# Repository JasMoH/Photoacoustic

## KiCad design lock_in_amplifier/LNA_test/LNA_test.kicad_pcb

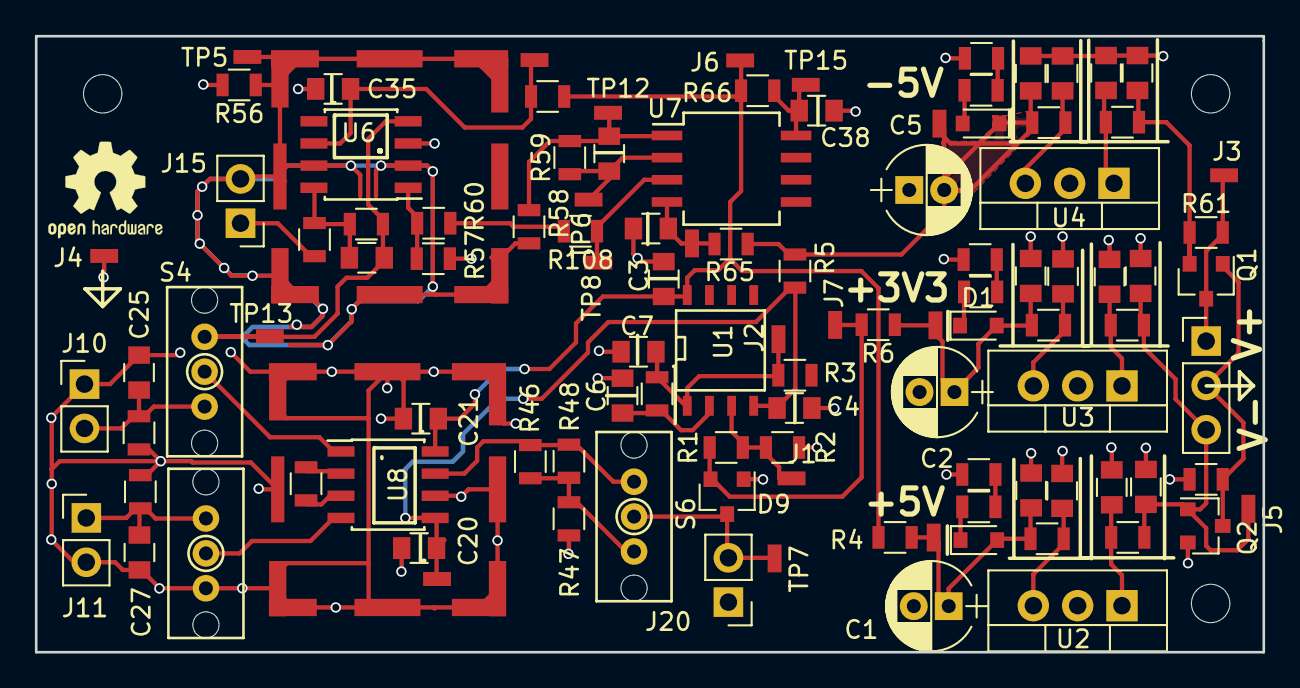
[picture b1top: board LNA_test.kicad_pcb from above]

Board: 2 copper layers, 70.4 x 35.3 mm, 109 parts (0 on the bottom side), 44 nets.

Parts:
C1, C2, C5: 10u; CP_Radial_D5.0mm_P2.00mm
C3, C4, C20, C21, C35, C37, C38: 0.1u; C_0805
C6, C7, C8, C9, C10, C11, C12, C13, C14, C15, C16, C17, C18, C19: 0.1uF; C_0805
C25, C27, C36: 10pF; C_0805
C39: C; C_0805
D1, D2, D3: LED; D_0805
D9: BAT54S; SOT-23
J1: vref-in; tyco_RCU_0603_Probe_Pad
J2: vref; tyco_RCU_0603_Probe_Pad
J3: V-IN; tyco_RCU_0603_Probe_Pad
J4: GND; tyco_RCU_0603_Probe_Pad
J5: V+IN; tyco_RCU_0603_Probe_Pad
J6: +5V; tyco_RCU_0603_Probe_Pad
J7: +3V3; tyco_RCU_0603_Probe_Pad
J8: -5V; tyco_RCU_0603_Probe_Pad
J10: A IN; Pin_Header_Straight_1x02_Pitch2.54mm
J11: B IN; Pin_Header_Straight_1x02_Pitch2.54mm
J12: POWER_IN; Pin_Header_Straight_1x03_Pitch2.54mm
J15: I IN; Pin_Header_Straight_1x02_Pitch2.54mm
J17, J38: RF_Shield_One_Piece; SMS-201
J19: +3V3 OUT; tyco_RCU_0603_Probe_Pad
J20: AMP OUT; Pin_Header_Straight_1x02_Pitch2.54mm
J46: -5V OUT; tyco_RCU_0603_Probe_Pad
J47: +5V OUT; tyco_RCU_0603_Probe_Pad
L1, L2, L3, L4, L5, L6, L7: 10uH; L_0805
Q1, Q2: DMN640L; SOT-23
R1, R2, R60: 10K; R_0805
R3, R4, R5, R6, R56, R57, R61, R62, R63, R65, R108: 0; R_0805
R7, R8, R9, R43, R44, R45, R47, R58, R64: 100; R_0805
R21: 6.04; R_0805
R46: 10k; R_0805
R48: 1M; R_0805
R49, R50: 10M; R_0805
R55: 100M; R_0805
R59, R66: R; R_0805
S4: A / I SEL; SPDT_OS102011MS2QN1
S5: B SEL; SPDT_OS102011MS2QN1
S6: LNA GAIN SEL; SPDT_OS102011MS2QN1
TP5: CURRENT GUARD; tyco_RCU_0603_Probe_Pad
TP6: CURRENT GUARD FB; tyco_RCU_0603_Probe_Pad
TP7: LNA OUT; tyco_RCU_0603_Probe_Pad
TP8: TIA GUARD BUFF IN; tyco_RCU_0603_Probe_Pad
TP11: TIAV+; tyco_RCU_0603_Probe_Pad
TP12: GBUFFOUT; tyco_RCU_0603_Probe_Pad
TP13: TIA_OUT; tyco_RCU_0603_Probe_Pad
TP14: GBUFV-; tyco_RCU_0603_Probe_Pad
TP15: GBUFFV+; tyco_RCU_0603_Probe_Pad
U1: LM833; SOIC-8-N
U2: lm7805; TO-220-3_Vertical
U3: LM7833; TO-220-3_Vertical
U4: lm7905; TO-220-3_Vertical
U6: lmp7721; SOIC-8_3.9x4.9mm_Pitch1.27mm
U7: LM833; SO-8_5.3x6.2mm_Pitch1.27mm
U8: AD8429; SOIC-8_3.9x4.9mm_Pitch1.27mm

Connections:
+3V3: C2.1, C18.1, D1.2, D9.2, J7.1, J19.1, L6.2, R1.1, R6.1, R6.2
+5V: C1.1, C3.2, C19.1, C21.2, D3.2, J6.1, J47.1, L7.2, R4.1, R4.2, R63.2, R66.1, U1.8, U8.8
-5V: C4.2, C5.2, C17.1, C20.1, D2.1, J8.1, J46.1, L5.2, R5.1, R5.2, R65.2, U1.4, U8.5
/sheet5A330121/GND_IN: J12.2, Q1.1, Q2.3, R62.2
/sheet5A330121/V+_IN: C8.1, C9.1, J5.1, J12.3, L2.1, L3.2, Q2.1
/sheet5A330121/V-_IN: J3.1, J12.1, Q1.3, R61.2
/sheet5A330123/GUARD: J15.2, J17.1, R56.1, R58.2, TP5.1, U6.2, U6.7
/sheet5A330123/I_IN: J15.1, R64.2
/sheet5A330123/amplifie_signal: D9.3, J20.2, S6.2, TP7.1
/sheet5A330123/in+: C27.2, J11.1, R50.1, S5.1
/sheet5A330123/in-: C25.2, J10.2, R49.1, S4.3
GND: C1.2, C2.2, C3.1, C4.1, C5.1, C6.2, C7.2, C8.2, C9.2, C10.2, C11.2, C12.2, C13.2, C14.2, C15.2, C16.2, C17.2, C18.2, C19.2, C20.2, C21.1, C25.1, C27.1, C35.1, C37.2, C38.1, D9.1, J4.1, J10.1, J11.2, J20.1, J38.1, Q2.2, R2.2, R8.2, R43.2, R45.2, R47.2, R49.2, R50.2, R56.2, R57.1, R62.1, S5.3, U2.2, U3.2, U4.2, U6.3, U8.6
unnamed: C6.1, L1.2, U1.2
unnamed: C7.1, J2.1, L1.1, R3.2, U1.1
unnamed: C10.1, L4.2, Q1.2, R61.1
unnamed: C11.1, L2.2, U2.1
unnamed: C12.1, L3.1, U3.1
unnamed: C13.1, L4.1, U4.1
unnamed: C14.1, L5.1, U4.3
unnamed: C15.1, L6.1, U3.3
unnamed: C16.1, L7.1, U2.3
unnamed: C35.2, R63.1, TP11.1, U6.6
unnamed: C36.1, R55.1, S4.1, TP13.1, U6.4
unnamed: C36.2, R55.2, R64.1, U6.8
unnamed: C37.1, R65.1, TP14.1, U7.4
unnamed: C38.2, R66.2, TP15.1, U7.8
unnamed: C39.1, R59.1, TP6.1, U7.2
unnamed: C39.2, R58.1, R59.2, TP12.1, U7.1
unnamed: D1.1, R44.1
unnamed: D2.2, R7.1
unnamed: D3.1, R9.1
unnamed: J1.1, R1.2, R2.1, U1.3
unnamed: R7.2, R8.1
unnamed: R21.1, U8.3
unnamed: R21.2, U8.2
unnamed: R9.2, R43.1
unnamed: R44.2, R45.1
unnamed: R46.1, R48.1, S6.1, U8.7
unnamed: R46.2, R47.1, R48.2, S6.3
unnamed: R57.2, R60.2, U6.1
unnamed: R108.1, TP8.1, U7.3
unnamed: R60.1, R108.2
unnamed: S4.2, U8.1
unnamed: S5.2, U8.4

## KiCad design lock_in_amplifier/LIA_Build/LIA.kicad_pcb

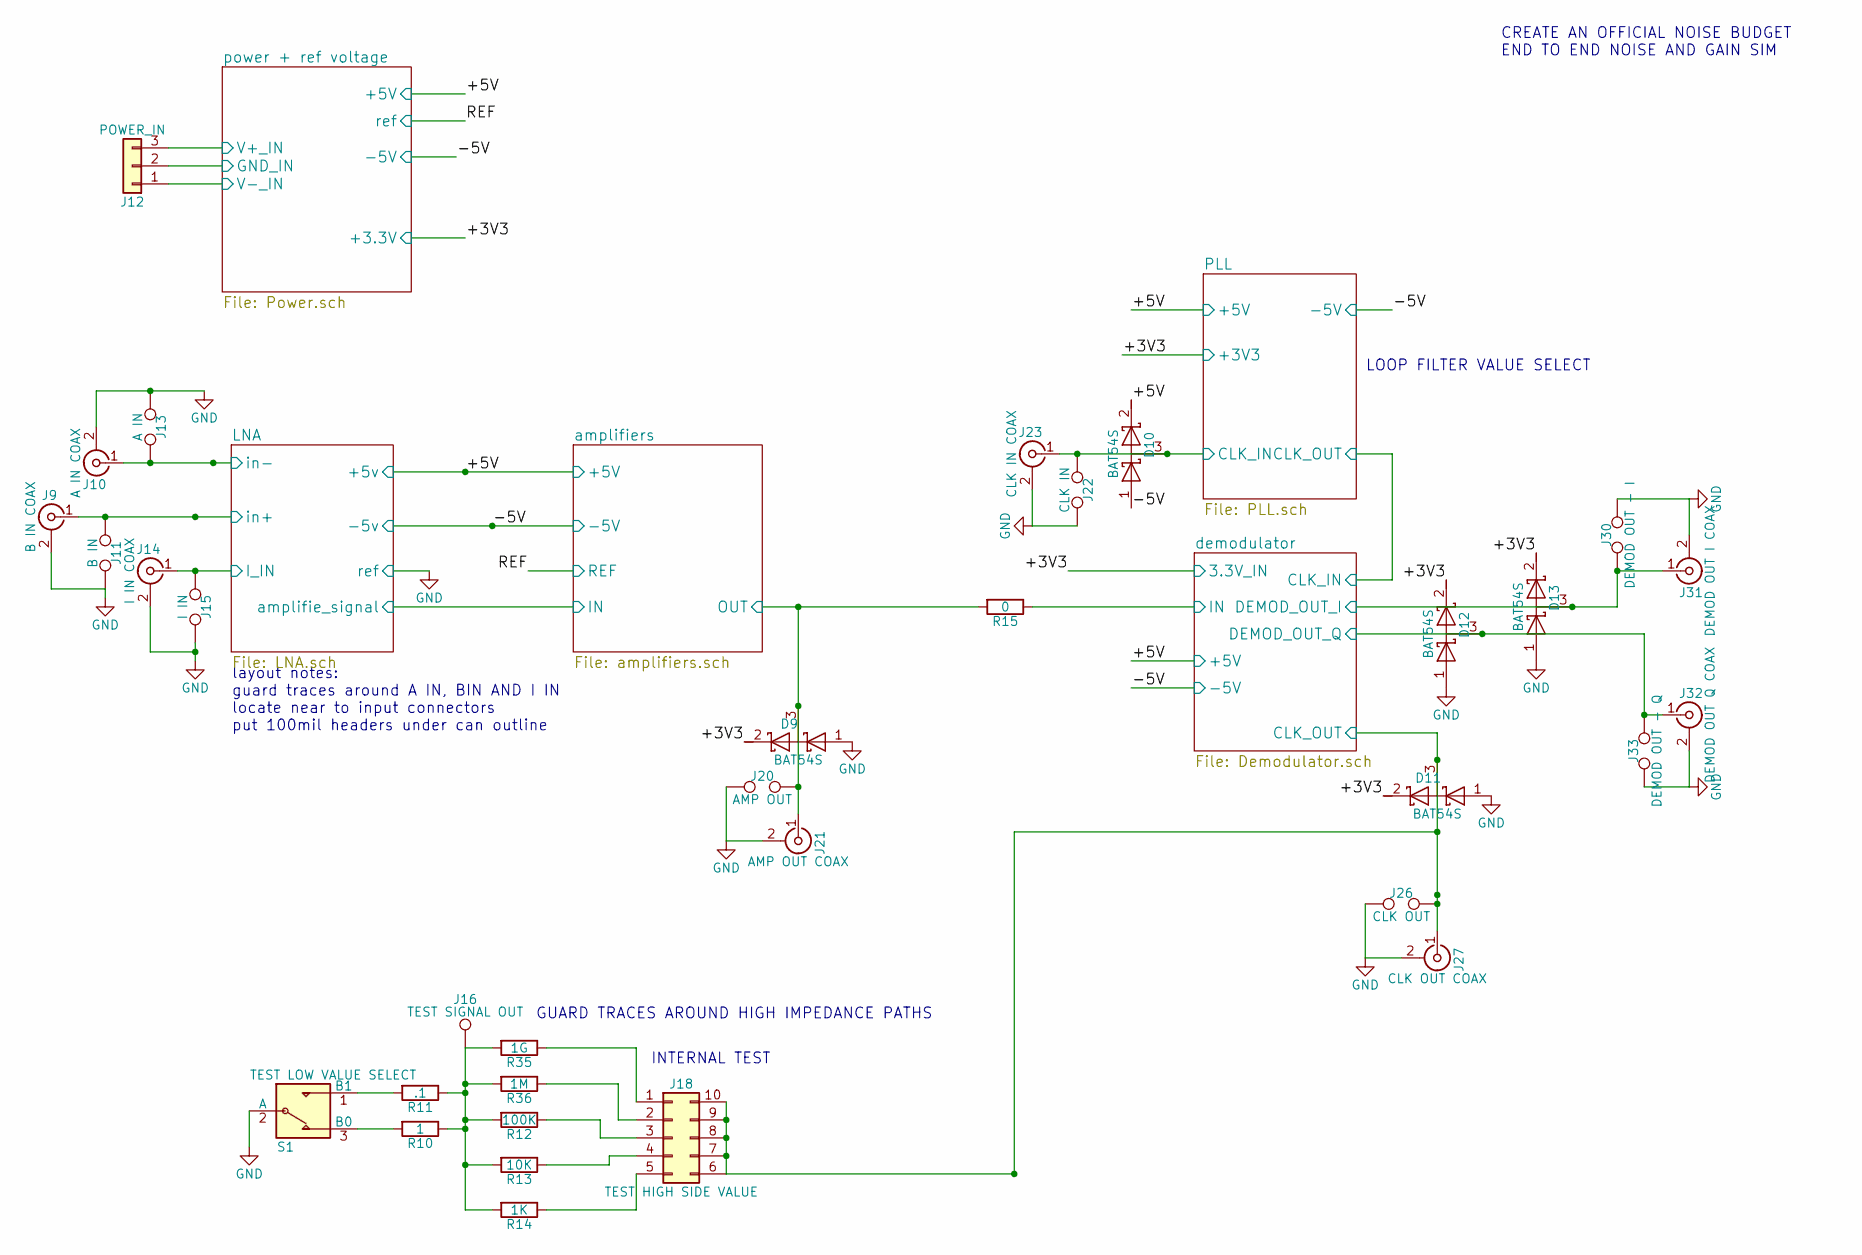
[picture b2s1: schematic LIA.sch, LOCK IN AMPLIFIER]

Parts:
D9, D10, D11, D12, D13: BAT54S; SOT-23
J9: B IN COAX; SMA_THT_Jack_Straight
J10: A IN COAX; SMA_THT_Jack_Straight
J11: B IN; Pin_Header_Straight_1x02_Pitch2.54mm
J12: POWER_IN; Pin_Header_Straight_1x03_Pitch2.54mm
J13: A IN; Pin_Header_Straight_1x02_Pitch2.54mm
J14: I IN COAX; SMA_THT_Jack_Straight
J15: I IN; Pin_Header_Straight_1x02_Pitch2.54mm
J16: TEST SIGNAL OUT; Pin_Header_Straight_1x01_Pitch1.00mm
J18: TEST HIGH SIDE VALUE; Pin_Header_Straight_2x05_Pitch2.54mm
J20: AMP OUT; Pin_Header_Straight_1x02_Pitch2.54mm
J21: AMP OUT COAX; SMA_THT_Jack_Straight
J22: CLK IN; Pin_Header_Straight_1x02_Pitch2.54mm
J23: CLK IN COAX; SMA_THT_Jack_Straight
J26: CLK OUT; Pin_Header_Straight_1x02_Pitch2.54mm
J27: CLK OUT COAX; SMA_THT_Jack_Straight
J30: DEMOD OUT - I; Pin_Header_Straight_1x02_Pitch2.54mm
J31: DEMOD OUT I COAX; SMA_THT_Jack_Straight
J32: DEMOD OUT Q COAX; SMA_THT_Jack_Straight
J33: DEMOD OUT - Q; Pin_Header_Straight_1x02_Pitch2.54mm
R10: 1; R_0805
R11: .1; R_0805
R12: 100K; R_0805
R13: 10K; R_0805
R14: 1K; R_0805
R15: 0; R_0805
R35: 1G; R_Axial_DIN0414_L11.9mm_D4.5mm_P15.24mm_Horizontal
R36: 1M; R_0805
S1: TEST LOW VALUE SELECT; Pin_Header_Straight_1x03_Pitch2.54mm

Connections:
+3V3: D9.2 (K), D11.2 (K), D12.2 (K), D13.2 (K); also elsewhere on the board
/LNA/I_IN: J14.1 (In), J15.1; also elsewhere on the board
/LNA/in+: J9.1 (In), J11.1; also elsewhere on the board
/LNA/in-: J10.1 (In), J13.2; also elsewhere on the board
/PLL/CLK_IN: D10.3 (common), J22.2, J23.1 (In); also elsewhere on the board
/amplifiers/OUT: D9.3 (common), J20.2, J21.1 (In), R15.2; also elsewhere on the board
/demodulator/CLK_OUT: D11.3 (common), J18.6, J18.7, J18.8, J18.9, J18.10, J26.2, J27.1 (In); also elsewhere on the board
/demodulator/DEMOD_OUT_I: D13.3 (common), J30.2, J31.1 (In); also elsewhere on the board
/demodulator/DEMOD_OUT_Q: D12.3 (common), J32.1 (In), J33.1; also elsewhere on the board
/demodulator/IN: R15.1; also elsewhere on the board
/power + ref voltage/GND_IN: J12.2; also elsewhere on the board
/power + ref voltage/V+_IN: J12.3; also elsewhere on the board
/power + ref voltage/V-_IN: J12.1; also elsewhere on the board
unnamed: J16.1, R10.1, R11.1, R12.2, R13.2, R14.2, R35.2, R36.2
unnamed: J18.1, R35.1
unnamed: J18.2, R36.1
unnamed: J18.3, R12.1
unnamed: J18.4, R13.1
unnamed: J18.5, R14.1
unnamed: R10.2, S1.3 (B0)
unnamed: R11.2, S1.1 (B1)

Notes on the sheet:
CREATE AN OFFICIAL NOISE BUDGET END TO END NOISE AND GAIN SIM
layout notes: guard traces around A IN, BIN AND I IN locate near to input connectors put 100mil headers under can outline
INTERNAL TEST
GUARD TRACES AROUND HIGH IMPEDANCE PATHS
LOOP FILTER VALUE SELECT

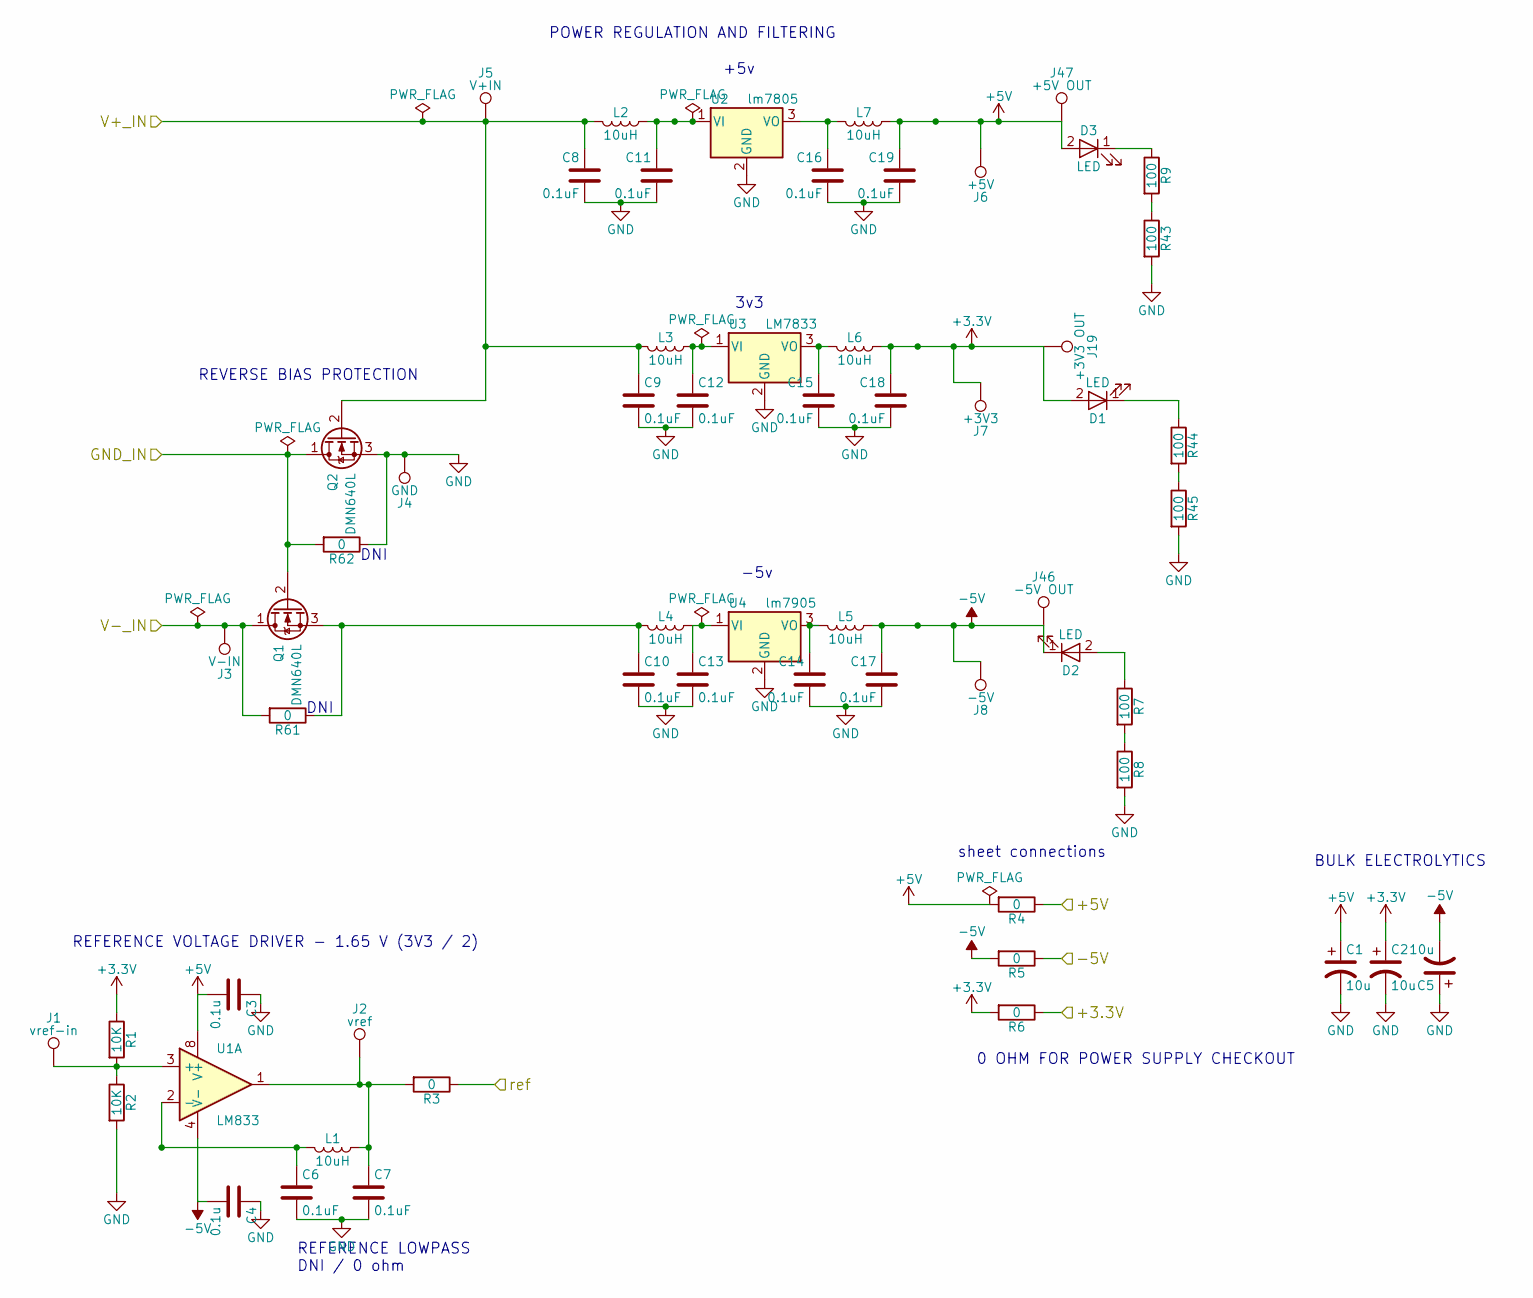
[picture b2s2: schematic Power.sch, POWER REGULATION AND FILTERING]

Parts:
C1, C2, C5: 10u; CP_Radial_D5.0mm_P2.00mm
C3, C4: 0.1u; C_0805
C6, C7, C8, C9, C10, C11, C12, C13, C14, C15, C16, C17, C18, C19: 0.1uF; C_0805
D1, D2, D3: LED; D_0805
J1: vref-in; tyco_RCU_0603_Probe_Pad
J2: vref; tyco_RCU_0603_Probe_Pad
J3: V-IN; tyco_RCU_0603_Probe_Pad
J4: GND; tyco_RCU_0603_Probe_Pad
J5: V+IN; tyco_RCU_0603_Probe_Pad
J6: +5V; tyco_RCU_0603_Probe_Pad
J7: +3V3; tyco_RCU_0603_Probe_Pad
J8: -5V; tyco_RCU_0603_Probe_Pad
J19: +3V3 OUT; tyco_RCU_0603_Probe_Pad
J46: -5V OUT; tyco_RCU_0603_Probe_Pad
J47: +5V OUT; tyco_RCU_0603_Probe_Pad
L1, L2, L3, L4, L5, L6, L7: 10uH; L_0805_HandSoldering
Q1, Q2: DMN640L; SOT-23
R1, R2: 10K; R_0805
R3, R4, R5, R6: 0; R_0805
R7, R8, R9, R43, R44, R45: 100; R_0805
R61, R62: 0
U1: LM833; SOIC-8-N
U2: lm7805; TO-220_Vertical
U3: LM7833; TO-220_Vertical
U4: lm7905; TO-220_Vertical

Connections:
+3V3: C2.1, C18.1, D1.2 (A), J7.1, J19.1, L6.2, R1.1, R6.1, R6.2; also elsewhere on the board
/REF: R3.1; also elsewhere on the board
/power + ref voltage/GND_IN: Q1.2 (G), Q2.1 (D), R62.2; also elsewhere on the board
/power + ref voltage/V+_IN: C8.1, C9.1, J5.1, L2.1, L3.2, Q2.2 (G); also elsewhere on the board
/power + ref voltage/V-_IN: J3.1, Q1.1 (D), R61.2; also elsewhere on the board
unnamed: C6.1, L1.2, U1.2 (-)
unnamed: C7.1, J2.1, L1.1, R3.2, U1.1
unnamed: C10.1, L4.2, Q1.3 (S), R61.1
unnamed: C11.1, L2.2, U2.1 (VI)
unnamed: C12.1, L3.1, U3.1 (VI)
unnamed: C13.1, L4.1, U4.1 (VI)
unnamed: C14.1, L5.1, U4.3 (VO)
unnamed: C15.1, L6.1, U3.3 (VO)
unnamed: C16.1, L7.1, U2.3 (VO)
unnamed: D1.1 (K), R44.1
unnamed: D2.2 (A), R7.1
unnamed: D3.1 (K), R9.1
unnamed: J1.1, R1.2, R2.1, U1.3 (+)
unnamed: R7.2, R8.1
unnamed: R9.2, R43.1
unnamed: R44.2, R45.1

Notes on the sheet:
REFERENCE VOLTAGE DRIVER - 1.65 V (3V3 / 2)
REFERENCE LOWPASS DNI / 0 ohm
BULK ELECTROLYTICS
3v3
+5v
-5v
sheet connections
0 OHM FOR POWER SUPPLY CHECKOUT
POWER REGULATION AND FILTERING
DNI
REVERSE BIAS PROTECTION

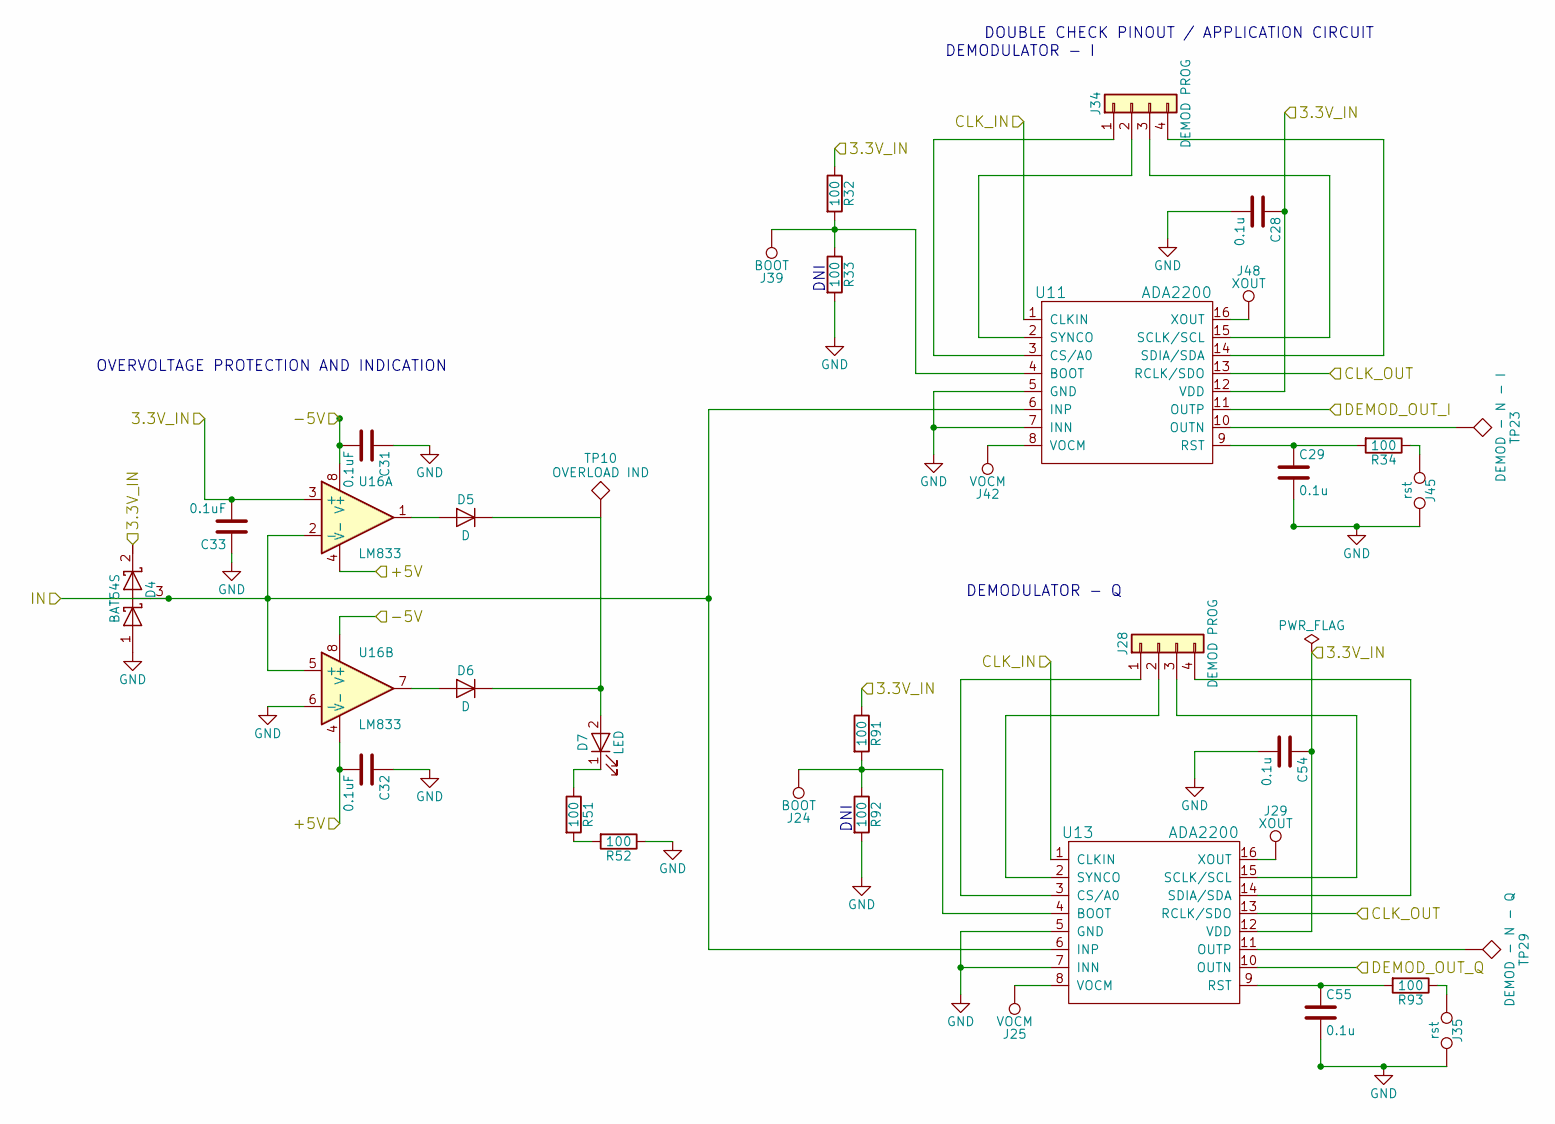
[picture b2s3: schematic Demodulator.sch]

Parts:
C28, C29, C54, C55: 0.1u; C_0805
C31, C32, C33: 0.1uF; C_0805
D4: BAT54S; SOT-23
D5, D6: D; D_0805
D7: LED; LED_0805
J24, J39: BOOT; tyco_RCU_0603_Probe_Pad
J25, J42: VOCM; tyco_RCU_0603_Probe_Pad
J28, J34: DEMOD PROG; Pin_Header_Straight_1x04_Pitch2.54mm
J29, J48: XOUT; tyco_RCU_0603_Probe_Pad
J35, J45: rst; Pin_Header_Straight_1x02_Pitch2.54mm
R32, R33, R34, R51, R52, R91, R92, R93: 100; R_0805
TP10: OVERLOAD IND; tyco_RCU_0603_Probe_Pad
TP23: DEMOD - N - I; tyco_RCU_0603_Probe_Pad
TP29: DEMOD - N - Q; tyco_RCU_0603_Probe_Pad
U11, U13: ADA2200; TSSOP-20_4.4x6.5mm_Pitch0.65mm
U16: LM833; SO-8_5.3x6.2mm_Pitch1.27mm

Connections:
+3V3: C28.1, C33.2, C54.1, D4.2 (K), R32.1, R91.1, U11.12 (VDD), U13.12 (VDD), U16.3 (+); also elsewhere on the board
/demodulator/CLK_IN: U11.1 (CLKIN), U13.1 (CLKIN); also elsewhere on the board
/demodulator/CLK_OUT: U11.13 (RCLK/SDO), U13.13 (RCLK/SDO); also elsewhere on the board
/demodulator/DEMOD_OUT_I: U11.11 (OUTP); also elsewhere on the board
/demodulator/DEMOD_OUT_Q: U13.10 (OUTN); also elsewhere on the board
/demodulator/IN: D4.3 (common), U11.6 (INP), U13.6 (INP), U16.2 (-), U16.5 (+); also elsewhere on the board
unnamed: C29.1, R34.2, U11.9 (RST)
unnamed: C55.1, R93.2, U13.9 (RST)
unnamed: D5.1 (K), D6.1 (K), D7.2 (A), TP10.1
unnamed: D5.2 (A), U16.1
unnamed: D6.2 (A), U16.7
unnamed: D7.1 (K), R51.1
unnamed: J24.1, R91.2, R92.1, U13.4 (BOOT)
unnamed: J25.1, U13.8 (VOCM)
unnamed: J28.1, U13.3 (CS/A0)
unnamed: J28.2, U13.2 (SYNCO)
unnamed: J28.3, U13.15 (SCLK/SCL)
unnamed: J28.4, U13.14 (SDIA/SDA)
unnamed: J29.1, U13.16 (XOUT)
unnamed: J34.1, U11.3 (CS/A0)
unnamed: J34.2, U11.2 (SYNCO)
unnamed: J34.3, U11.15 (SCLK/SCL)
unnamed: J34.4, U11.14 (SDIA/SDA)
unnamed: J35.1, R93.1
unnamed: J39.1, R32.2, R33.1, U11.4 (BOOT)
unnamed: J42.1, U11.8 (VOCM)
unnamed: J45.1, R34.1
unnamed: J48.1, U11.16 (XOUT)
unnamed: R51.2, R52.2
unnamed: TP23.1, U11.10 (OUTN)
unnamed: TP29.1, U13.11 (OUTP)

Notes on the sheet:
DNI
DOUBLE CHECK PINOUT / APPLICATION CIRCUIT
DEMODULATOR - I
OVERVOLTAGE PROTECTION AND INDICATION
DEMODULATOR - Q

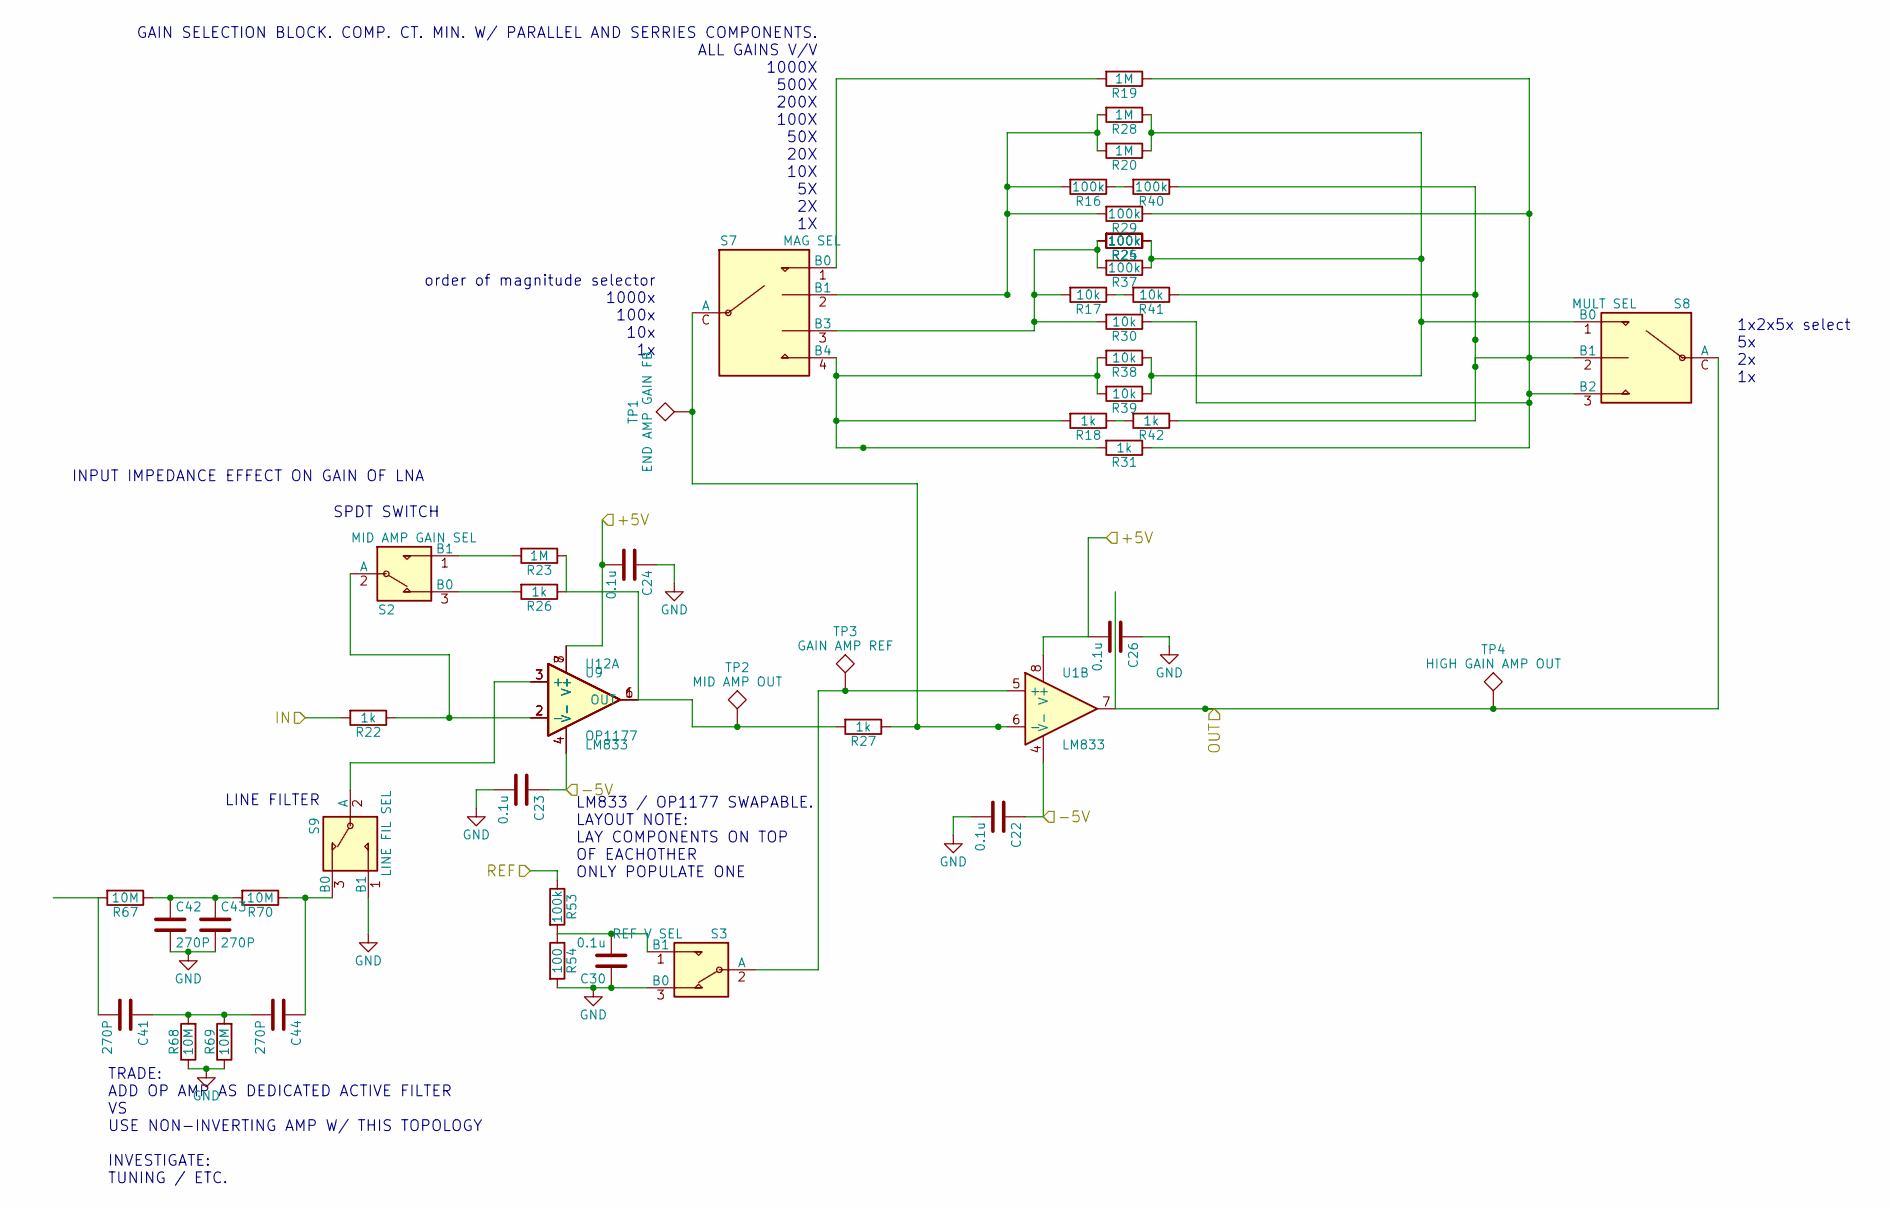
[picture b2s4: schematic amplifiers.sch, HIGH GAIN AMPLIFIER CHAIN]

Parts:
C22, C23, C24, C26, C30: 0.1u; C_0805
C41, C42, C43, C44: 270P
R16, R24, R25, R29, R37, R40: 100k; R_0805
R17, R30, R38, R39, R41: 10k; R_0805
R18, R22, R26, R27, R31, R42: 1k; R_0805
R19, R20, R23, R28: 1M; R_0805
R53: 100k
R54: 100
R67, R68, R69, R70: 10M
S2: MID AMP GAIN SEL; SPDT_OS102011MS2QN1
S3: REF V SEL; SPDT_OS102011MS2QN1
S7: MAG SEL; SP4T_C&K_SS-14D0839-VG
S8: MULT SEL; SP3T_CK_SS-14D0839-VG
S9: LINE FIL SEL; SPDT_OS102011MS2QN1
TP1: END AMP GAIN FB
TP2: MID AMP OUT
TP3: GAIN AMP REF
TP4: HIGH GAIN AMP OUT
U1: LM833; SOIC-8-N
U9: OP1177; MSOP-8-1EP_3x3mm_Pitch0.65mm
U12: LM833

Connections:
/REF: R53.1; also elsewhere on the board
/amplifiers/IN: R22.2; also elsewhere on the board
/amplifiers/OUT: S8.C (A), TP4.1, U1.7; also elsewhere on the board
unnamed: C30.2, R53.2, R54.1, S3.1 (B1)
unnamed: C41.1, C44.2, R68.2, R69.2
unnamed: C42.1, C43.1, R67.1, R70.2
unnamed: R16.1, R40.2
unnamed: R16.2, R20.2, R28.2, R29.2, S7.2 (B1)
unnamed: R17.1, R41.2
unnamed: R17.2, R24.2, R25.2, R30.2, R37.2, S7.3 (B3)
unnamed: R18.1, R42.2
unnamed: R18.2, R31.2, R38.2, R39.2, S7.4 (B4)
unnamed: R19.1, R29.1, R30.1, R31.1, R40.1, R41.1, R42.1, S8.2 (B1), S8.3 (B2)
unnamed: R19.2, S7.1 (B0)
unnamed: R20.1, R24.1, R25.1, R28.1, R37.1, R38.1, R39.1, S8.1 (B0)
unnamed: R23.1, R26.1, R27.2, TP2.1, U9.6 (OUT), U12.1
unnamed: R23.2, S2.1 (B1)
unnamed: R26.2, S2.3 (B0)
unnamed: R27.1, S7.C (A), TP1.1, U1.6 (-)
unnamed: S3.2 (A), TP3.1, U1.5 (+)

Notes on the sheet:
SPDT SWITCH
GAIN SELECTION BLOCK. COMP. CT. MIN. W/ PARALLEL AND SERRIES COMPONENTS. ALL GAINS V/V 1000X 500X 200X 100X 50X 20X 10X 5X 2X 1X
1x2x5x select 5x 2x 1x
order of magnitude selector 1000x 100x 10x 1x
LINE FILTER
INPUT IMPEDANCE EFFECT ON GAIN OF LNA
TRADE: ADD OP AMP AS DEDICATED ACTIVE FILTER VS USE NON-INVERTING AMP W/ THIS TOPOLOGY INVESTIGATE: TUNING / ETC.
LM833 / OP1177 SWAPABLE. LAYOUT NOTE: LAY COMPONENTS ON TOP OF EACHOTHER ONLY POPULATE ONE

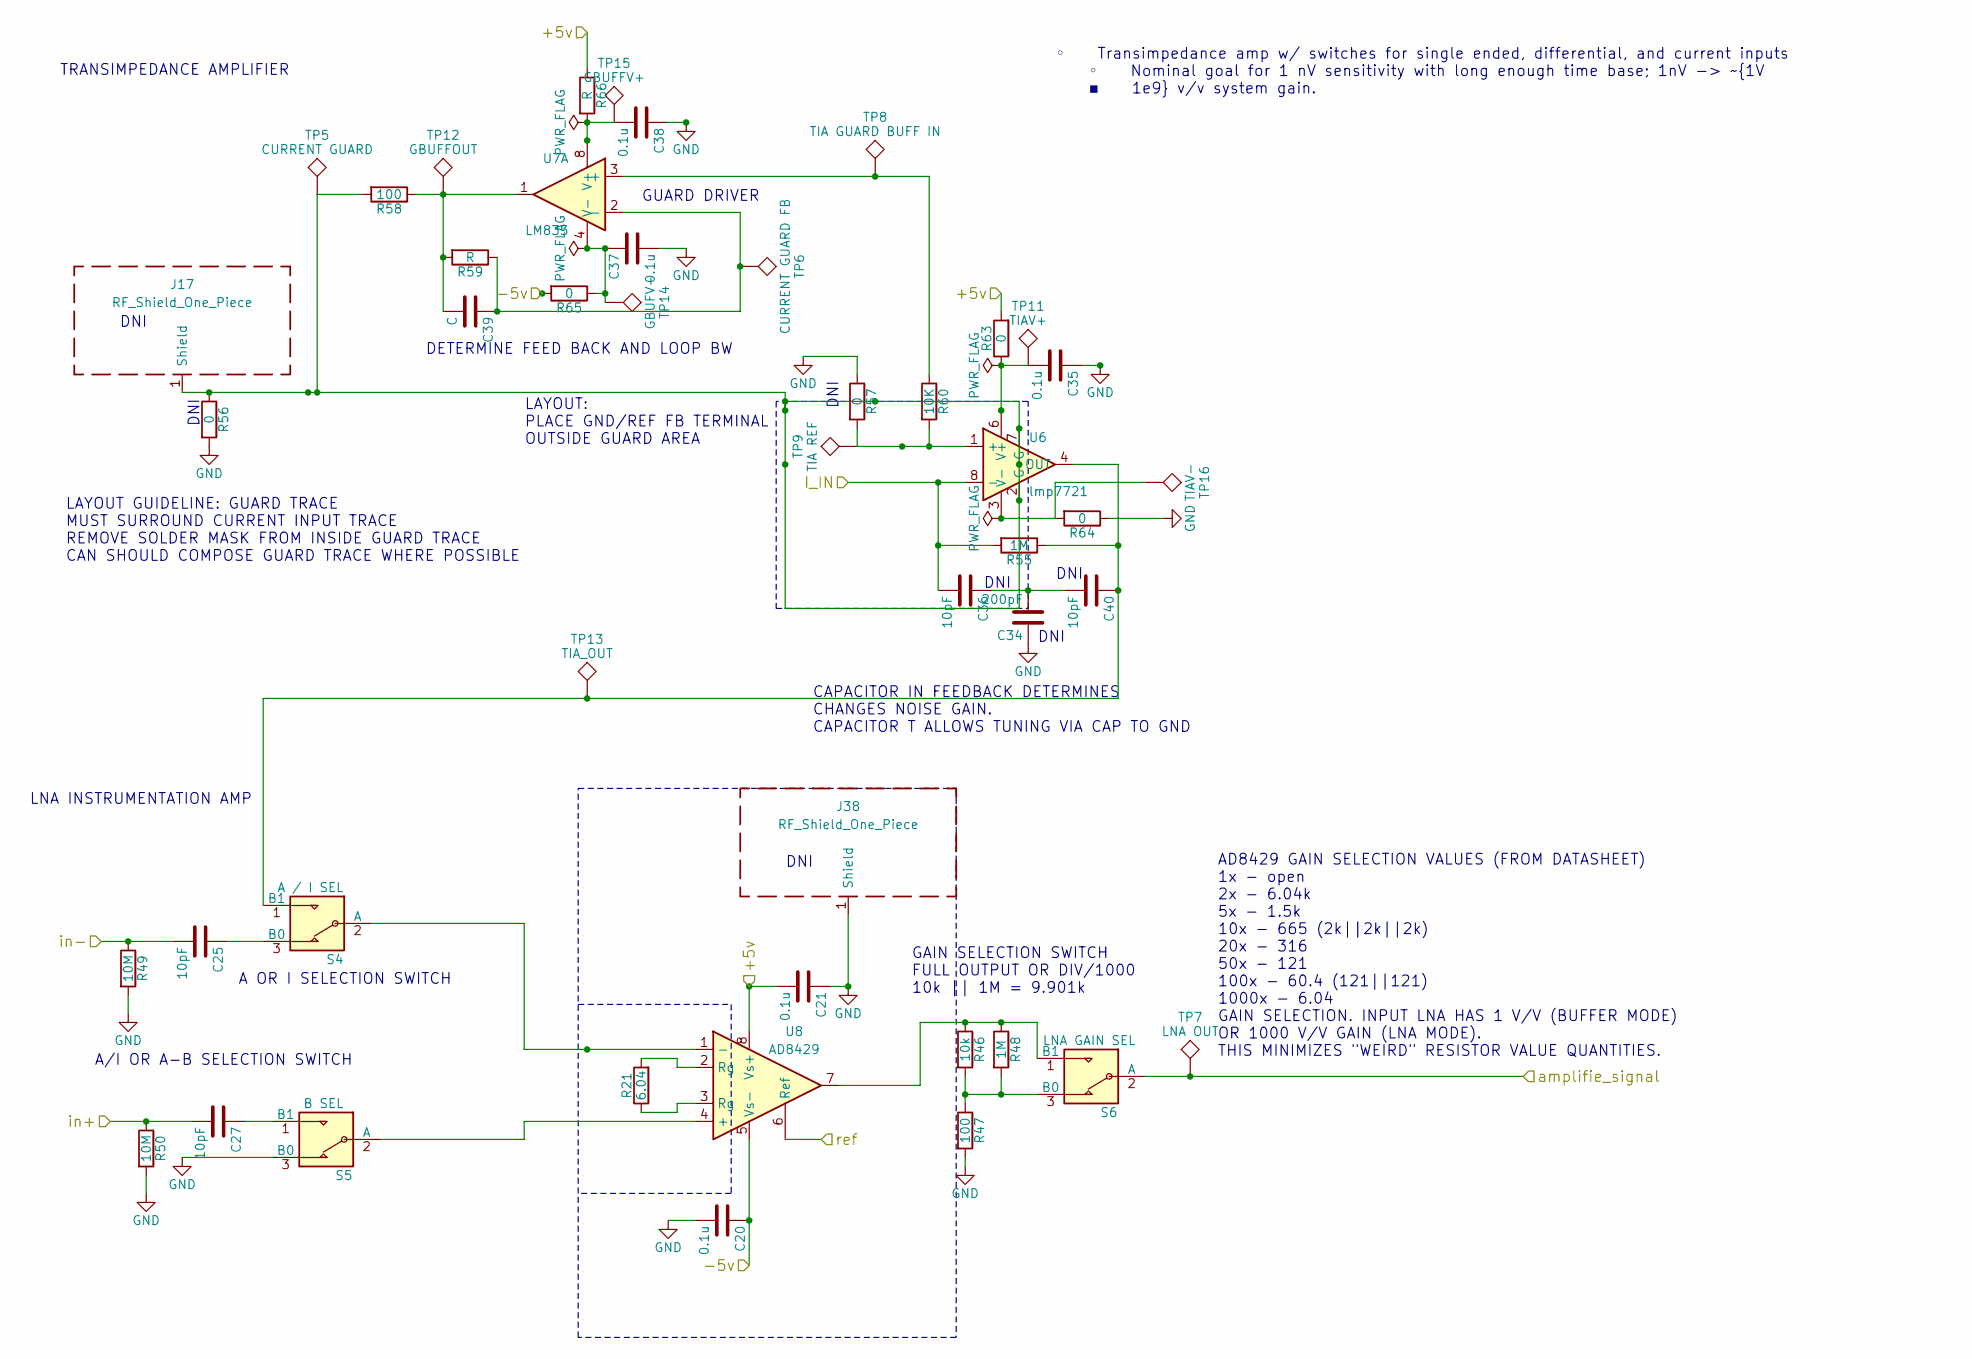
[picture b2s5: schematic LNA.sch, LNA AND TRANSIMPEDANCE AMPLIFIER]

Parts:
C20, C21, C35, C37, C38: 0.1u; C_0805
C25, C27, C36, C40: 10pF
C34: 200pF
C39: C
J17, J38: RF_Shield_One_Piece; SMS-201
R21: 6.04; R_0805
R46: 10k
R47, R58: 100
R48, R55: 1M
R49, R50: 10M
R56, R57, R63, R64, R65: 0
R59, R66: R
R60: 10K
S4: A / I SEL; SPDT_OS102011MS2QN1
S5: B SEL; SPDT_OS102011MS2QN1
S6: LNA GAIN SEL; SPDT_OS102011MS2QN1
TP5: CURRENT GUARD
TP6: CURRENT GUARD FB
TP7: LNA OUT
TP8: TIA GUARD BUFF IN
TP9: TIA REF
TP11: TIAV+
TP12: GBUFFOUT
TP13: TIA_OUT
TP14: GBUFV-
TP15: GBUFFV+
TP16: TIAV-
U6: lmp7721; MSOP-8-1EP_3x3mm_Pitch0.65mm
U7: LM833
U8: AD8429; SOIC-8_3.9x4.9mm_Pitch1.27mm

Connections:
/LNA/I_IN: C36.2, R55.2, U6.8 (-); also elsewhere on the board
/LNA/in+: C27.2, R50.1; also elsewhere on the board
/LNA/in-: C25.2, R49.1; also elsewhere on the board
/amplifiers/IN: S6.2 (A), TP7.1; also elsewhere on the board
unnamed: C25.1, S4.3 (B0)
unnamed: C27.1, S5.1 (B1)
unnamed: C34.2, C36.1, C40.2
unnamed: C35.2, R63.1, TP11.1, U6.6 (V+)
unnamed: C39.1, R59.1, TP6.1, U7.2 (-)
unnamed: C39.2, R58.1, R59.2, TP12.1, U7.1
unnamed: C40.1, R55.1, S4.1 (B1), TP13.1, U6.4 (OUT)
unnamed: J17.1, R56.1, R58.2, TP5.1, U6.2 (G), U6.7 (G)
unnamed: R21.1, U8.3 (Rg)
unnamed: R21.2, U8.2 (Rg)
unnamed: R46.1, R48.1, S6.1 (B1), U8.7
unnamed: R46.2, R47.1, R48.2, S6.3 (B0)
unnamed: R57.2, R60.2, TP9.1, U6.1 (+)
unnamed: R60.1, TP8.1, U7.3 (+)
unnamed: R64.2, TP16.1, U6.3 (V-)
unnamed: S4.2 (A), U8.1 (-)
unnamed: S5.2 (A), U8.4 (+)

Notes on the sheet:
LNA INSTRUMENTATION AMP
◦ Transimpedance amp w/ switches for single ended, differential, and current inputs ◦ Nominal goal for 1 nV sensitivity with long enough time base; 1nV -> ~1V ▪ 1e9 v/v system gain.
AD8429 GAIN SELECTION VALUES (FROM DATASHEET) 1x - open 2x - 6.04k 5x - 1.5k 10x - 665 (2k||2k||2k) 20x - 316 50x - 121 100x - 60.4 (121||121) 1000x - 6.04 GAIN SELECTION. INPUT LNA HAS 1 V/V (BUFFER MODE) OR 1000 V/V GAIN (LNA MODE). THIS MINIMIZES "WEIRD" RESISTOR VALUE QUANTITIES.
TRANSIMPEDANCE AMPLIFIER
A OR I SELECTION SWITCH
A/I OR A-B SELECTION SWITCH
GAIN SELECTION SWITCH FULL OUTPUT OR DIV/1000 10k || 1M = 9.901k
LAYOUT GUIDELINE: GUARD TRACE MUST SURROUND CURRENT INPUT TRACE REMOVE SOLDER MASK FROM INSIDE GUARD TRACE CAN SHOULD COMPOSE GUARD TRACE WHERE POSSIBLE
GUARD DRIVER
DNI
LAYOUT: PLACE GND/REF FB TERMINAL OUTSIDE GUARD AREA
DETERMINE FEED BACK AND LOOP BW
CAPACITOR IN FEEDBACK DETERMINES CHANGES NOISE GAIN. CAPACITOR T ALLOWS TUNING VIA CAP TO GND

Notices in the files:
instrumentation amp bob/inst_amp.kicad_pcb:
LICENSE: GPLv3
GPLv3
lock_in_amplifier/LNA_test/LNA_test.kicad_pcb:
GPL V3.0
